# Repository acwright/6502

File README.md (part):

6502-COB
========

An **AC6502** retro-style 8-bit computer based on the **65C02** microprocessor.

> 📖 **Guide:** [AC6502 Documentation](https://acwright.github.io/6502-DOCS/) — the user's and programmer's guide for the whole family.
> See [COB's page in the family appendix](https://acwright.github.io/6502-DOCS/family/cob).

---

## Table of Contents

- [Overview](#overview)
- [Architecture](#architecture)
- [Systems](#systems)
- [Software](#software)
- [Hardware](#hardware)
  - [Backplanes](#backplanes)
  - [Cards](#cards)
  - [Helpers](#helpers)
- [Firmware](#firmware)
  - [KEH Controller](#keh-controller)
  - [PS2 Keyboard Controller](#ps2-keyboard-controller)
  - [STP Controller](#stp-controller)
- [CAD](#cad)
- [Production](#production)
- [Schematics](#schematics)
- [Checking the schematics](#checking-the-schematics)
- [Libraries](#libraries)
- [Bill of Materials](#bill-of-materials)
  - [Backplane](#backplane)
  - [Backplane Helper](#backplane-helper)
  - [Backplane Pro](#backplane-pro)
  - [Blinkenlights Card](#blinkenlights-card)
  - [Breadboard Helper](#breadboard-helper)
  - [Clock Helper](#clock-helper)
  - [CPU Card](#cpu-card)
  - [CPU Card Pro](#cpu-card-pro)
  - [DB25 Helper](#db25-helper)
  - [GPIO Breadboard Helper](#gpio-breadboard-helper)
  - [GPIO Card](#gpio-card)
  - [GPIO Helper](#gpio-helper)
  - [Joystick Helper](#joystick-helper)
  - [Keyboard Encoder Helper](#keyboard-encoder-helper)
  - [Keyboard Helper](#keyboard-helper)
  - [LCD Board](#lcd-board)
  - [LCD Card](#lcd-card)
  - [Mega Helper](#mega-helper)
  - [Memory Card](#memory-card)
  - [Prototype Card](#prototype-card)
  - [PS2 Helper](#ps2-helper)
  - [RAM Card](#ram-card)
  - [RTC Card](#rtc-card)
  - [Serial Card](#serial-card)
  - [Serial Card Pro](#serial-card-pro)
  - [Sound Card](#sound-card)
  - [Storage Card](#storage-card)
  - [Storage Card Pro](#storage-card-pro)
  - [VERA Helper](#vera-helper)
  - [VGA Card](#vga-card)
  - [VGA Card Pro](#vga-card-pro)
  - [Video Card](#video-card)
  - [Video Card Pro](#video-card-pro)
- [Purchase](#purchase)
- [License](#license)

---

## Overview

The AC6502 ecosystem is a family of open-source, 65C02-based computers sharing a common architecture, memory map, and [BIOS](https://github.com/acwright/6502-BIOS). Each computer in the family is purpose-built for a different use case but runs the same software and firmware.

The **COB** (Computer on a Backplane) is a full-featured modular desktop computer. It features a real 65C02 CPU, a backplane architecture with expandable card slots, up to 544KB RAM, composite or VGA video output, CompactFlash or SD storage, a real-time clock, and support for PS/2 keyboards, matrix keyboards, and Atari 2600-compatible joysticks.

## Architecture

All AC6502 computers share:

- **CPU**: 65C02 (or accurate emulation)
- **Memory**: 32KB RAM + 32KB ROM, with optional banked RAM expansion
- **Memory Map**: Standardized across the ecosystem — zero page, stack, I/O space ($8000–$9FFF), system ROM, and interrupt vectors at $FFFA–$FFFF
- **Bus**: 16-bit address bus, 8-bit bidirectional data bus, standard 65C02 control signals (RW, PHI2, RESET, IRQ, NMI, RDY, SYNC)
- **BIOS**: A common [BIOS](https://github.com/acwright/6502-BIOS) provides the kernel, monitor, and BASIC interpreter across all systems

## Systems

| Project | Description |
|---------|-------------|
| [6502-ACE](https://github.com/acwright/6502-ACE) | All-in-one Computer Experience — A single board computer |
| [6502-COB](https://github.com/acwright/6502-COB) | Computer On a Backplane — Modular desktop computer with expandable card slots (YOU ARE HERE) |
| [6502-DEV](https://github.com/acwright/6502-DEV) | Development Environment Vehicle — Emulation-based dev system |
| [6502-KIM](https://github.com/acwright/6502-KIM) | Keypad Input Monitor - KIM-1 inspired minimal computer |
| [6502-VCS](https://github.com/acwright/6502-VCS) | Video Computer System — Cartridge-based retro gaming console |

## Software

| Project | Description |
|---------|-------------|
| [6502-BIOS](https://github.com/acwright/6502-BIOS) | The shared BIOS (kernel, monitor, BASIC) for all AC6502 computers |
| [6502-EMULATOR](https://github.com/acwright/6502-EMULATOR) | Emulator for the whole family — desktop app, browser build, and a command line for scripted runs |
| [6502-PRG](https://github.com/acwright/6502-PRG) | Template project for writing assembly language programs |
| [6502-CRT](https://github.com/acwright/6502-CRT) | Template project for writing assembly language cartridges |
| [6502-ASM](https://github.com/acwright/6502-ASM) | Assembly language example programs and demos |
| [6502-BAS](https://github.com/acwright/6502-BAS) | BASIC program listings |
| [6502-WOZMON](https://github.com/acwright/6502-WOZMON) | Wozmon as a standalone ROM |
| [6502-NOP](https://github.com/acwright/6502-NOP) | An all-NOP ROM, for probing a board during bring-up |
| [6502-DOCS](https://github.com/acwright/6502-DOCS) | The documentation site — the guide, the printable reference cards, branding and label artwork |
| [cffs](https://github.com/acwright/cffs) | Builds CompactFlash disk images for the BIOS filesystem |
| [bastok](https://github.com/acwright/bastok) | Tokenizes BASIC listings into `.prg` images, and back |
| [bin2woz](https://github.com/acwright/bin2woz) | Converts a binary into a Wozmon serial upload |

## Hardware

This repository contains KiCad 7.0+ PCB designs for the backplanes, cards, and helpers that make up the COB system.

### Backplanes

**`Hardware/Backplane/`** — Passive backplane providing 5 card slots with full bus interconnect across all slots.

**`Hardware/Backplane Pro/`** — Enhanced backplane with integrated clock generation, reset circuitry, and power distribution plus 5 card slots. Rev 1.1 moves to entirely through-hole components and adds an onboard power switch and DC barrel jack input.

**`Hardware/Backplane Helper/`** — Adds additional card slots to expand the total backplane configuration up to 12 slots.

### Cards

**`Hardware/CPU Card/`** — Hosts the 65C02 CPU in a card form factor for backplane-based COB systems.

**`Hardware/CPU Card Pro/`** — Hosts a 65816 16-bit CPU (backward-compatible with 65C02). *(Untested)*

**`Hardware/Memory Card/`** — Provides 32KB SRAM and 32KB EEPROM with address decoding logic for COB systems using the CPU Card.

**`Hardware/RAM Card/`** — 512KB banked RAM expansion organized as two 256KB banks with 256 × 1KB windows each.

**`Hardware/RTC Card/`** — Real-time clock via Dallas DS1511Y with battery backup and 256 bytes of battery-backed SRAM.

**`Hardware/GPIO Card/`** — General-purpose I/O via 65C22 VIA supporting keyboards, joysticks, timers, and custom devices.

**`Hardware/Serial Card/`** — RS-232 serial communication via 65C51 ACIA and MAX232 level shifter.
Female DB-9 wired as **DCE**, so a straight-through cable reaches a PC. `DCD` and `DSR` are tied to
ground; `DTR` is not connected. The `CTS EN` jumper (J4) picks whether the ACIA's `CTS` comes from
ground or from the cable — **ground is the default**, which leaves the transmitter always free to
send.

**`Hardware/Serial Card Pro/`** — Enhanced serial card with full modem control signals (DTR, DCD, DSR).
Male DB-9 wired as **DTE**, like a PC, so reaching a laptop needs a **null-modem** cable — unlike the
plain Serial Card. `CTS`, `DSR` and `DTR` always reach the cable; the `DCD EN` jumper picks ground or
the cable for `DCD` — **ground is the default**.

**The handshake lines are not decoration.** On a real R6551, measured on a KIM in 2026: `CTS` high
stops the transmitter dead, and `DCD` high stops the receiver and the arriving byte is lost. A card
jumpered to take either from the cable, plugged into something that does not assert them, looks like
a dead board — no banner, no echo — until the line comes back. Ground is the default for exactly
that reason.

**`Hardware/VGA Card/`** — VGA 640×480 video output via Raspberry Pi Pico running [Pico9918](https://github.com/visrealm/pico9918) with TMS9918A-compatible graphics modes.

**`Hardware/VGA Card Pro/`** — Fully programmable VGA output using Pi Pico with custom firmware. *(Untested)*

**`Hardware/Video Card/`** — Composite video output via TMS9918A Video Display Processor with 16KB video RAM.

**`Hardware/Video Card Pro/`** — Enhanced composite video card. *(Untested)*

**`Hardware/Sound Card/`** — 3-voice SID audio output via ARMSID module with RCA line-level output.

**`Hardware/Storage Card/`** — CompactFlash storage interface supporting up to 128GB via IDE-compatible protocol.

**`Hardware/Storage Card Pro/`** — SD card (up to 32GB) and 16MB onboard SPI flash storage interface. *(Untested, experimental — the stock BIOS has no driver for it; see [STP Controller](#stp-controller))*

**`Hardware/LCD Card/`** — 16×2 character LCD display via 65C22 VIA in 4-bit or 8-bit mode.

**`Hardware/Blinkenlights Card/`** — Visual bus monitoring with LEDs showing address bus (16), data bus (8), and control signals (8) in real time.

**`Hardware/Prototype Card/`** — Blank prototyping area with integrated breadboard and full bus access headers.

### Helpers

**`Hardware/Keyboard Encoder Helper/`** — ATmega1284p-based dual keyboard encoder supporting PS/2 keyboard and 8×8 matrix keyboard simultaneously via 65C22 VIA.

**`Hardware/PS2 Helper/`** — ATmega328p-based PS/2 keyboard bridge that drives an MT8808 analog crosspoint switch to emulate a matrix keyboard. Its output is a raw 8×8 matrix and feeds the matrix inputs of a Keyboard Encoder Helper, which is what talks to the 65C22 VIA — not the VIA directly.

**`Hardware/Keyboard Helper/`** — 64-key matrix keyboard with Atari 2600-compatible joystick support.

**`Hardware/GPIO Helper/`** — 8 buttons and 8 LEDs for testing and debugging GPIO Card connections.

**`Hardware/GPIO Breadboard Helper/`** — Breadboard interface adapter for the GPIO Card.

**`Hardware/Joystick Helper/`** — Atari 2600-style dual joystick connector and interface board.

**`Hardware/Clock Helper/`** — Manual clock control providing single-step, free-run, and halt modes for debugging real CPU systems.

**`Hardware/DB25 Helper/`** — GPIO to DB25 connector adapter for external device interfacing.

**`Hardware/Breadboard Helper/`** — Exposes the full AC6502 bus to a breadboard for prototyping and experimentation.

**`Hardware/Mega Helper/`** — Arduino Mega 2560 interface adapter for the AC6502 bus.

**`Hardware/LCD Board/`** — 320×240 TFT LCD display (ILI9341) interfaced via 65C22 VIA. *(Untested)*

**`Hardware/VERA Helper/`** — VERA FPGA video module adapter for the AC6502 bus.

## Firmware

This repository contains [PlatformIO](https://platformio.org/)-based firmware for the COB system's microcontroller helpers.

### KEH Controller
`Firmware/KEH Controller/`

Firmware for the ATmega1284p on the Keyboard Encoder Helper. Provides:

- Simultaneous PS/2 keyboard and 8×8 matrix keyboard scanning
- ASCII conversion with modifier key support (Shift, Ctrl)
- Buffered, debounced input handling
- Parallel I/O to the AC6502 bus via 65C22 VIA

See [Firmware/KEH Controller/README.md](./Firmware/KEH%20Controller/README.md) for setup and usage instructions.

### PS2 Keyboard Controller
`Firmware/PS2 Keyboard Controller/`

Firmware for the ATmega328p on the PS2 Helper. Provides:

- Interrupt-driven PS/2 keyboard scan code reading
- MT8808 analog crosspoint switch matrix control
- Make/break detection and extended scan code support
- Function key emulation via FN key combinations

The MT8808 closes row/column contacts in place of physical key switches, so this
card connects to the **matrix inputs of a Keyboard Encoder Helper**, not to a
65C22 VIA. The encoder does the scanning and ASCII conversion; wired straight to
a VIA the card produces nothing, as the BIOS has no matrix-scanning code.

See [Firmware/PS2 Keyboard Controller/README.md](./Firmware/PS2%20Keyboard%20Controller/README.md) for setup and usage instructions.

### STP Controller
`Firmware/STP Controller/`

Firmware for the ATmega328p on the Storage Card Pro. Provides:

- Memory-mapped SPI controller for 6502 bus access
- Support for SD card, 16MB SPI flash, and external SPI devices
- Dual-speed SPI (4 MHz normal operation, 400 kHz initialization)
- PHI2-synchronized interface for reliable 6502 communication

⚠️ **Experimental.** The Storage Card Pro is not part of the default I/O set the
BIOS probes for, and no COB machine is built around it today. The BIOS storage
slot expects eight True IDE CompactFlash registers at `$8C00–$8C07`; this card
presents two SPI registers instead, so a stock BIOS reports `NO DEVICE` for every
storage path. Using it needs a modified BIOS or software that drives the two
registers directly.

See [Firmware/STP Controller/README.md](./Firmware/STP%20Controller/README.md) for setup and usage instructions.

## CAD
`CAD/`

3D-printable enclosure parts and laser-cut top panels for the COB system.

## Production
`Production/`

JLCPCB-ready Gerber files and BOM/CPL for PCB fabrication and assembly.

## Schematics
`Schematics/`

PDF schematics for each board.

## Checking the schematics
`Tests/check-schematics.mjs`

The RAM Card's bank latch decides which kilobyte of its 512 KB each window shows, and a latch that loads on the wrong address corrupts a bank without any sign. The ACE's equivalent latch was wrong twice while its gates looked right on paper, so this script checks the logic instead of reading it. It asks KiCad for the card's netlist, builds the glue logic from the gates it finds there, fits the card's jumpers, and drives every address, as a read and as a write, with PHI2 high and low. That is 262,144 bus states. For each one it compares the RAM's chip select, read and write strobes and A18, and the latch enable, against the memory map, and checks that the card drives the data bus only on a read of its own window. A net that nothing drives counts as a failure, so a missing wire fails too.

It checks the RAM Card Rev 1.0 with both windows jumpered, IO 1 (`$8000`) and IO 2 (`$8400`), which is the only setting Rev 1.0 supports: R1 and R2 pull the window selects to ground, so a window left without a jumper is selected at every address.

Run it after any change to a checked schematic:

```sh
node Tests/check-schematics.mjs
```

It needs Node.js and KiCad's `kicad-cli`, which it finds on the `PATH`, at the macOS default location, or through a `KICAD_CLI` environment variable. It takes a few seconds, prints `ok` or `FAIL` for each check with example bus states for any failure, and exits non-zero on a failure.

## Libraries
`Libraries/`

Shared KiCad symbol and footprint libraries used across all AC6502 hardware projects.

## Bill of Materials

### Backplane

| Reference | Qty | Value | Description | DigiKey | Mouser |
|-----------|-----|-------|-------------|---------|--------|
| J1–J5 | 5 | 6502 Card Connector | Card Edge 2×20 | [A31723-ND](https://www.digikey.com/en/products/filter?keywords=A31723-ND) | [571-5-5530843-4](https://www.mouser.com/ProductDetail/571-5-5530843-4) |
| J6, J7 | 2 | 6502 Bus | Bus Connector 2×20 | [732-5401-ND](https://www.digikey.com/en/products/filter?keywords=732-5401-ND) | |

### Backplane Helper

| Reference | Qty | Value | Description | DigiKey | Mouser |
|-----------|-----|-------|-------------|---------|--------|
| J1, J2 | 2 | 6502 Card Connector | Card Edge 2×20 | [A31723-ND](https://www.digikey.com/en/products/filter?keywords=A31723-ND) | [571-5-5530843-4](https://www.mouser.com/ProductDetail/571-5-5530843-4) |
| J3 | 1 | 6502 Bus | Bus Connector 2×20 | [732-5401-ND](https://www.digikey.com/en/products/filter?keywords=732-5401-ND) | |

### Backplane Pro

#### Rev 1.1

| Reference | Qty | Value | Description | Mouser |
|-----------|-----|-------|-------------|--------|
| C1, C3 | 2 | 10uF | Polarized capacitor | |
| C2 | 1 | 100nF | Unpolarized capacitor | |
| D1 | 1 | LED | Power LED 3mm | |
| J1 | 1 | 5V DC | DC Barrel Jack | [640-DCJ200-10-A-K1-K](https://www.mouser.com/ProductDetail/640-DCJ200-10-A-K1-K) |
| J2–J4, J7, J8 | 5 | 6502 Card Connector | Card Edge 2×20 | [571-5-5530843-4](https://www.mouser.com/ProductDetail/571-5-5530843-4) |
| J5 | 1 | CLOCK ENBL SW | Pin Header 1×2 | |
| J6 | 1 | RESET SW | Pin Header 1×2 | |
| J9 | 1 | 6502 Bus | Bus Connector 2×20 | |
| JP1 | 1 | Solder Jumper | Solder Jumper 2-pole | |
| Q1 | 1 | 2N3904 | NPN Transistor TO-92 | |
| R1 | 1 | 330 | Resistor | |
| R2 | 1 | 1M | Resistor | |
| R3 | 1 | 47k | Resistor | |
| R4 | 1 | 10k | Resistor | |
| R5 | 1 | 1k | Resistor | |
| SW1 | 1 | POWER | SPDT Power Switch | [612-400MSP1R6BLKM6QE](https://www.mouser.com/ProductDetail/612-400MSP1R6BLKM6QE) |
| SW2 | 1 | RESET | Tact Push Button 5mm | |
| U1 | 1 | LM555 | Timer SOIC-8 | |
| X1 | 1 | OCXO-14 | Crystal Oscillator DIP-14 | |

#### Rev 1.0

| Reference | Qty | Value | Description | LCSC | DigiKey | Mouser |
|-----------|-----|-------|-------------|------|---------|--------|
| C1, C3–C14 | 13 | 100nF | Unpolarized capacitor | [C49678](https://www.lcsc.com/search?q=C49678) | | |
| C2 | 1 | 10uF | Polarized capacitor | [C7171](https://www.lcsc.com/search?q=C7171) | | |
| D1 | 1 | 1N5819 | Schottky Diode SOD-323F | [C191023](https://www.lcsc.com/search?q=C191023) | | |
| D2 | 1 | LED | LED 0805 | [C2297](https://www.lcsc.com/search?q=C2297) | | |
| J1 | 1 | PWR_SW | JST XH 1×2 | | [455-2247-ND](https://www.digikey.com/en/products/filter?keywords=455-2247-ND) | |
| J2 | 1 | USB-C | USB 2.0 Type-C Receptacle | [C2988369](https://www.lcsc.com/search?q=C2988369) | | |
| J3 | 1 | RESET_SW | JST XH 1×2 | | [455-2247-ND](https://www.digikey.com/en/products/filter?keywords=455-2247-ND) | |
| J4 | 1 | CLOCK_ENBL_SW | JST XH 1×2 | | [455-2247-ND](https://www.digikey.com/en/products/filter?keywords=455-2247-ND) | |
| J5–J9 | 5 | 6502 Card Connector | Card Edge 2×20 | | [A31723-ND](https://www.digikey.com/en/products/filter?keywords=A31723-ND) | [571-5-5530843-4](https://www.mouser.com/ProductDetail/571-5-5530843-4) |
| J10 | 1 | 6502 Bus | Bus Connector 2×20 | | | |
| Q1 | 1 | SS8050 | NPN Transistor SOT-23 | [C2150](https://www.lcsc.com/search?q=C2150) | | |
| R1 | 1 | 1M | Resistor | [C17514](https://www.lcsc.com/search?q=C17514) | | |
| R2 | 1 | 47k | Resistor | [C17713](https://www.lcsc.com/search?q=C17713) | | |
| R3 | 1 | 1k | Resistor | [C17513](https://www.lcsc.com/search?q=C17513) | | |
| R4 | 1 | 10k | Resistor | [C17414](https://www.lcsc.com/search?q=C17414) | | |
| R5, R6 | 2 | 5.1k | Resistor | [C27834](https://www.lcsc.com/search?q=C27834) | | |
| R7 | 1 | 330 | Resistor | [C17630](https://www.lcsc.com/search?q=C17630) | | |
| SW1 | 1 | Reset | Push Button | [C318884](https://www.lcsc.com/search?q=C318884) | | |
| U1 | 1 | LM555xM | Timer SOIC-8 | [C7593](https://www.lcsc.com/search?q=C7593) | | |
| X1 | 1 | OCXO-14 | Crystal Oscillator DIP-14 | | | |

### Blinkenlights Card

| Reference | Qty | Value | Description | LCSC |
|-----------|-----|-------|-------------|------|
| C1–C4 | 4 | 100nF | Unpolarized capacitor | [C49678](https://www.lcsc.com/search?q=C49678) |
| D1–D25 | 25 | LED | LED 0805 | [C2297](https://www.lcsc.com/search?q=C2297) |
| D26, D27 | 2 | LED | LED 0805 | [C2295](https://www.lcsc.com/search?q=C2295) |
| D28–D30 | 3 | LED | LED 0805 | [C2296](https://www.lcsc.com/search?q=C2296) |
| D31, D32 | 2 | LED | LED 0805 | [C2293](https://www.lcsc.com/search?q=C2293) |
| R1–R32 | 32 | 330 | Resistor | [C17630](https://www.lcsc.com/search?q=C17630) |
| U1, U2, U4 | 3 | 74HC573 | 8-bit Latch SOIC-20 | [C5608](https://www.lcsc.com/search?q=C5608) |
| U3 | 1 | 74HC04 | Hex Inverter SOIC-14 | [C5590](https://www.lcsc.com/search?q=C5590) |

### Breadboard Helper

| Reference | Qty | Value | Description | DigiKey |
|-----------|-----|-------|-------------|---------|
| J1 | 1 | 6502 Bus | Bus Connector 2×20 | [732-5401-ND](https://www.digikey.com/en/products/filter?keywords=732-5401-ND) |
| J2, J3 | 2 | Pin Header | Pin Header 1×20 | |

### Clock Helper

| Reference | Qty | Value | Description |
|-----------|-----|-------|-------------|
| C1 | 1 | 100nF | Capacitor |
| D1, D2 | 2 | LED | LED 3mm |
| J1 | 1 | IO | Pin Header 1×5 |
| R1–R5 | 5 | 1k | Resistor |
| R6–R8 | 3 | 330 | Resistor |
| SW1, SW2 | 2 | XKB5858-Z | DPDT Toggle Switch |
| SW3 | 1 | XKB5858-W | DPDT Toggle Switch |
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
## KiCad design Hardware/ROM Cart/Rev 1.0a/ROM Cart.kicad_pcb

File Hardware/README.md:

6502 Hardware
=============

This folder contains KiCad hardware designs for all PCBs in the 6502 project. Each design includes complete schematics, PCB layouts, and component libraries.

---

## Table of Contents

- [Overview](#overview)
- [Folder Structure](#folder-structure)
- [Hardware Categories](#hardware-categories)
- [Design Standards](#design-standards)
- [Assembly Notes](#assembly-notes)
- [Revision History](#revision-history)

---

## Overview

The 6502 project hardware is organized into four main categories:

1. **Boards**: Core system boards (mainboards, backplanes, development boards)
2. **Cards**: Peripheral expansion cards that plug into backplane slots
3. **Helpers**: Interface boards that provide specific functionality or connectors
4. **Carts**: Cartridge boards for ROM images

All designs are created using **KiCad 7.0+** and optimized for manufacturing by **JLCPCB**. Designs use a mix of surface-mount (SMD) and through-hole (DIP/TH) components for optimal balance of manufacturability and hobbyist assembly.

---

## Folder Structure

```
Hardware/
├── <BoardName>/
│   ├── Rev X.X/
│       ├── <BoardName>.kicad_pro    # KiCad project file
│       ├── <BoardName>.kicad_sch    # Schematic file
│       ├── <BoardName>.kicad_pcb    # PCB layout file
│       ├── fp-lib-table              # Footprint library table
│       └── sym-lib-table             # Symbol library table
└── ...
```

Each board folder contains one or more revision subfolders. Always use the latest revision unless specifically maintaining compatibility with older versions.

---

## Design Standards

All hardware designs follow these standards for consistency and manufacturability:

### PCB Specifications

**Layers:**
- Simple boards: 2-layer

**Dimensions:**
- Card width: 100mm
- Card height: 60mm
- Board width: 100mm
- Board height: 100mm
- Helper width: 100mm
- Helper height: 50mm
- PCB thickness: 1.6mm standard

**Trace Width:**
- Signal traces: 0.254mm (10 mil) minimum, 0.381mm (15 mil) typical
- Power traces: 0.508mm (20 mil) minimum, wider for high current
- Clearance: 0.254mm (10 mil) minimum

**Vias:**
- Standard: 0.6mm drill, 1.0mm pad
- Power: 0.8mm drill, 1.2mm pad
- Minimum: 0.3mm drill, 0.6mm pad

**JLCPCB Compatibility:**
- All designs pass JLCPCB design rules (see Production folder)
- Component selection optimized for JLCPCB assembly catalog
- Alternative footprints provided where JLCPCB parts unavailable

### Component Selection

**IC Packages:**
- Through-hole (DIP): For CPUs, RAM, ROM, socketed ICs
- SMD (SOIC, TSSOP, QFN): For modern ICs, microcontrollers, buffers

**Passive Components:**
- SMD: 0805 or 1206 packages (hand-solderable)
- Through-hole: 1/8W resistors, radial capacitors (when space allows)

**Connectors:**
- Through-hole: For all connectors (mechanical stress consideration)
- IDC headers: 2.54mm pitch for ribbon cables
- Card edge: Gold-plated fingers for backplane cards

### Schematic Conventions

**Net Naming:**
- Address bus: A0-A15
- Data bus: D0-D7
- Control signals: PHI2, RWB, RESB, IRQB, NMIB, etc.
- Power: +5V or VCC, GND
- Chip enables: CS, CSB (active low)

**Component References:**
- U: Integrated circuits
- R: Resistors
- C: Capacitors
- D: Diodes
- Q: Transistors
- J: Connectors/headers
- SW: Switches
- LED: LEDs
- Y: Crystals/oscillators

**Component Values:**
- Resistors: Ohms (100R, 1K, 10K)
- Capacitors: Farads (100nF, 10μF, 100μF)
- Inductors: Henries (10μH, 100μH)

---

## Assembly Notes

### Component Orientation

**ICs in DIP sockets:**
- Pin 1 indicator (notch or dot) must align with socket and PCB marking
- CPU, RAM, ROM: Check datasheets for pin 1 location

**Electrolytic capacitors:**
- Polarity marked on PCB (+ and -)
- Negative stripe on capacitor body aligns with - on PCB

**Diodes:**
- Cathode band aligns with band on PCB silkscreen

**LEDs:**
- Longer lead (anode) to + pad
- Flat side (cathode) to - pad or square pad

### Soldering Tips

**Through-hole:**
- Insert component from top, bend leads on bottom
- Apply soldering iron to pad + lead simultaneously
- Feed solder to junction (not to iron tip)
- Remove iron then solder wire
- Ideal joint: shiny, concave fillet

**SMD (if hand-soldering):**
- Use fine-tip soldering iron (conical tip)
- Apply flux to pads
- Tack one corner pin first
- Solder remaining pins
- Check for bridges with magnification
- Use solder wick to remove bridges

**IC sockets:**
- Tack opposite corner pins first
- Solder all remaining pins
- Check alignment before soldering all pins

### DRC (Design Rules Check) Verification

Before ordering PCBs, run DRC in KiCad:
1. Open PCB layout in KiCad
2. Select Tools → Design Rules Checker
3. Load JLCPCB design rules (if available in Production folder)
4. Run DRC
5. Fix all errors (warnings acceptable if understood)

Common errors:
- Trace too thin (minimum 0.127mm outer layer)
- Clearance too small (minimum 0.127mm)
- Via drill too small (minimum 0.3mm)
- Silkscreen over pads (warnings, JLCPCB will clip automatically)

---

## Revision History

### Rev 0.0 (Prototyping - 2024)

**Boards:**
- Dev Board

**Known Issues (Rev 1.0):**
- Dev Board 0.0 uses TXS0108 level shifters which were found to be unpredictable on the 6502 bus with some cards

### Rev 1.0 (Initial Release - 2024)

**Boards:**
- Initial designs for all boards
- Backplane, Backplane Pro, Main Board, Dev Board

**Cards:**
- CPU Card, Memory Card, Video Card, VGA Card, Serial Card
- GPIO Card, Sound Card, Storage Card
- Blinkenlights Card, LCD Card, Prototype Card
- RAM Card, RTC Card

**Helpers:**
- Keyboard Encoder Helper, PS2 Helper
- Keypad Helper, Keyboard Helper
- Clock Helper, GPIO Helper, Breadboard Helper
- Joystick Helper, DB25 Helper
- Backplane Helper, Mega Helper

**Carts:**
- ROM Cart

**Known Issues (Rev 1.0):**
- None

### Rev 1.1 (Planned - Future)

**Improvements:**
- TODO

---

## Working with Hardware Designs

### Opening in KiCad

1. Install [KiCad 7.0 or later](https://www.kicad.org/)
2. Clone this repository or download specific board folder
3. Navigate to `Hardware/<BoardName>/Rev X.X/`
4. Open `<BoardName>.kicad_pro` in KiCad

### Viewing Schematics

1. With project open, click "Schematic Editor" icon
2. Navigate multi-sheet schematics with sheet hierarchy (left panel)
3. Use Find tool (Ctrl+F / Cmd+F) to locate specific nets or components

### Viewing PCB Layout

1. With project open, click "PCB Editor" icon
2. Use 3D Viewer (View → 3D Viewer) to see board in 3D
3. Toggle layers (right panel) to examine inner layers, silkscreen, etc.

### Exporting Production Files

See [Production README](../Production/README.md) for detailed export instructions.

Quick export (from PCB Editor):
- Gerbers: File → Fabrication Outputs → Gerbers
- Drill files: File → Fabrication Outputs → Drill Files
- BOM: File → Fabrication Outputs → BOM
- Pick and Place: File → Fabrication Outputs → Footprint Position (.pos) File

---

**For more information, see:**
- [Main README](../README.md) - Project overview and system descriptions
- [Production README](../Production/README.md) - Manufacturing and ordering
- [Firmware README](../Firmware/README.md) - Firmware for microcontroller-based boards
- [Schematics README](../Schematics/README.md) - Schematic viewing and conventions

---

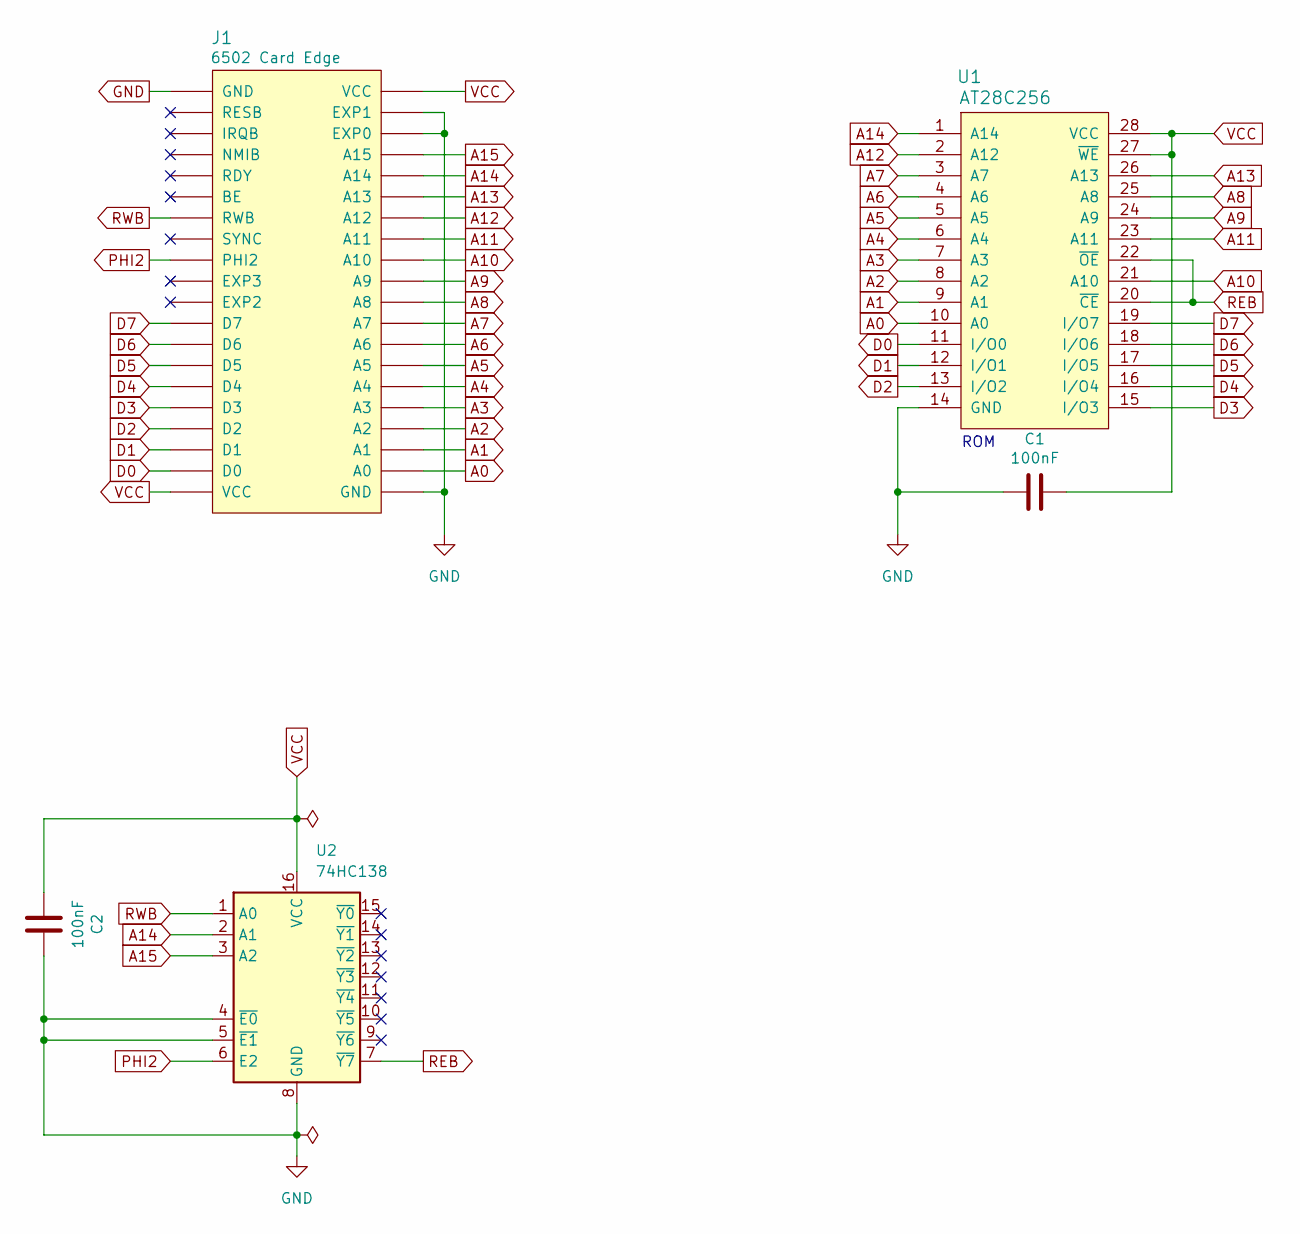
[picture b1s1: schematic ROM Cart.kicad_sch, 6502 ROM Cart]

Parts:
C1, C2: 100nF; C_Disc_D5.0mm_W2.5mm_P5.00mm
J1: 6502 Card Edge
U1: AT28C256; DIP-28_W15.24mm_Socket_LongPads
U2: 74HC138; DIP-16_W7.62mm_Socket_LongPads

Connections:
A0: J1.A0, U1.10 (A0)
A1: J1.A1, U1.9 (A1)
A2: J1.A2, U1.8 (A2)
A3: J1.A3, U1.7 (A3)
A4: J1.A4, U1.6 (A4)
A5: J1.A5, U1.5 (A5)
A6: J1.A6, U1.4 (A6)
A7: J1.A7, U1.3 (A7)
A8: J1.A8, U1.25 (A8)
A9: J1.A9, U1.24 (A9)
A10: J1.A10, U1.21 (A10)
A11: J1.A11, U1.23 (A11)
A12: J1.A12, U1.2 (A12)
A13: J1.A13, U1.26 (A13)
A14: J1.A14, U1.1 (A14), U2.2 (A1)
A15: J1.A15, U2.3 (A2)
D0: J1.D0, U1.11 (I/O0)
D1: J1.D1, U1.12 (I/O1)
D2: J1.D2, U1.13 (I/O2)
D3: J1.D3, U1.15 (I/O3)
D4: J1.D4, U1.16 (I/O4)
D5: J1.D5, U1.17 (I/O5)
D6: J1.D6, U1.18 (I/O6)
D7: J1.D7, U1.19 (I/O7)
GND: C1.2, C2.2, J1.EXP0, J1.EXP1, J1.GND, U1.14 (GND), U2.4 (~E0), U2.5 (~E1), U2.8 (GND)
PHI2: J1.PHI2, U2.6 (E2)
RB: U1.20 (~CE), U1.22 (~OE), U2.7 (~Y7)
RWB: J1.RWB, U2.1 (A0)
VCC: C1.1, C2.1, J1.VCC, U1.27 (~WE), U1.28 (VCC), U2.16 (VCC)

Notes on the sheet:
ROM

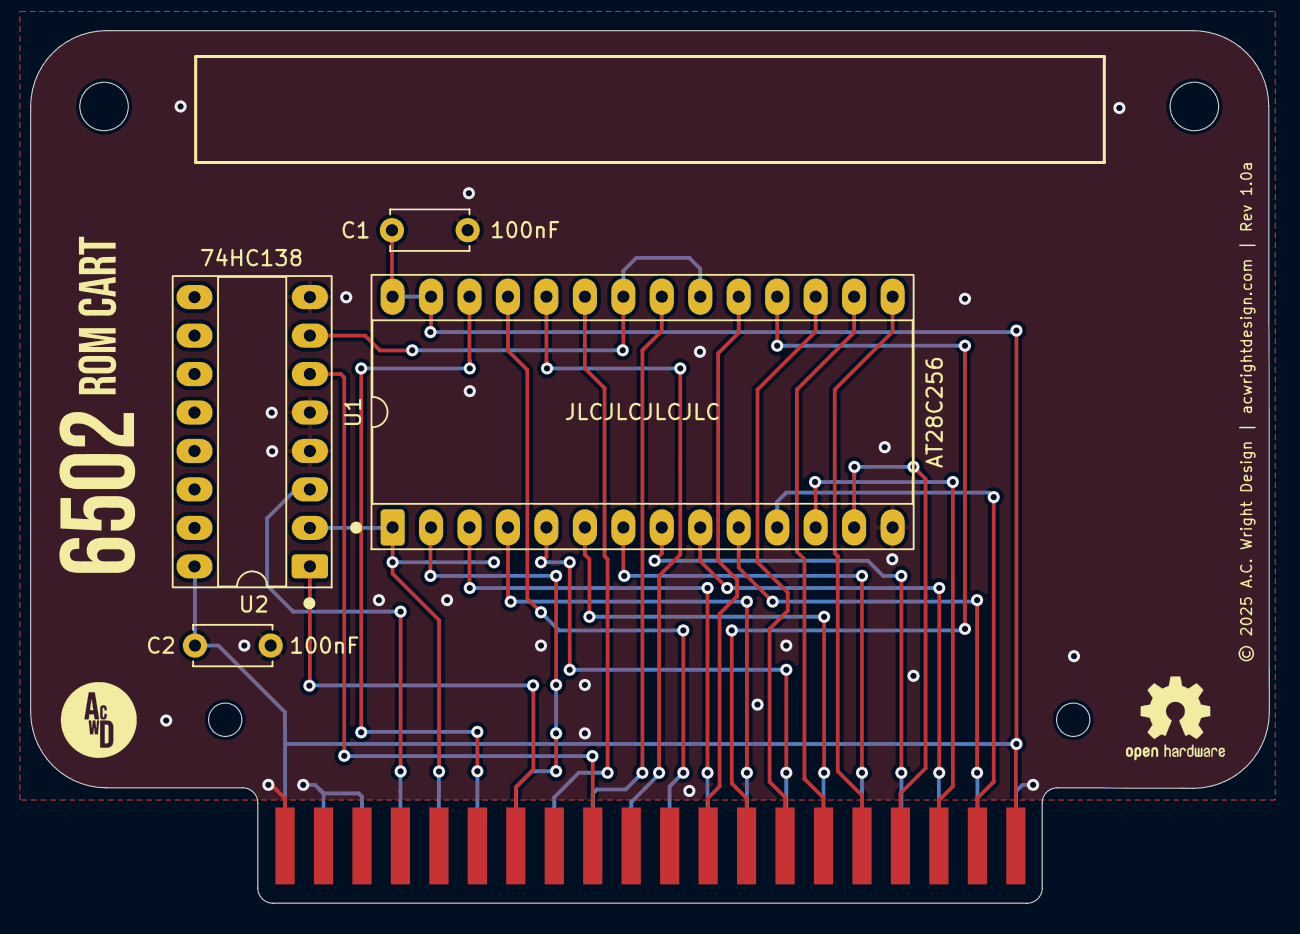
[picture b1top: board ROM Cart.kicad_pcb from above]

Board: 2 copper layers, 81.8 x 57.6 mm, 9 parts (0 on the bottom side), 29 nets.

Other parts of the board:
H1, H2: MountingHole; MountingHole_3.2mm_M3
H3, H4: MountingHole; MountingHole_2.2mm_M2

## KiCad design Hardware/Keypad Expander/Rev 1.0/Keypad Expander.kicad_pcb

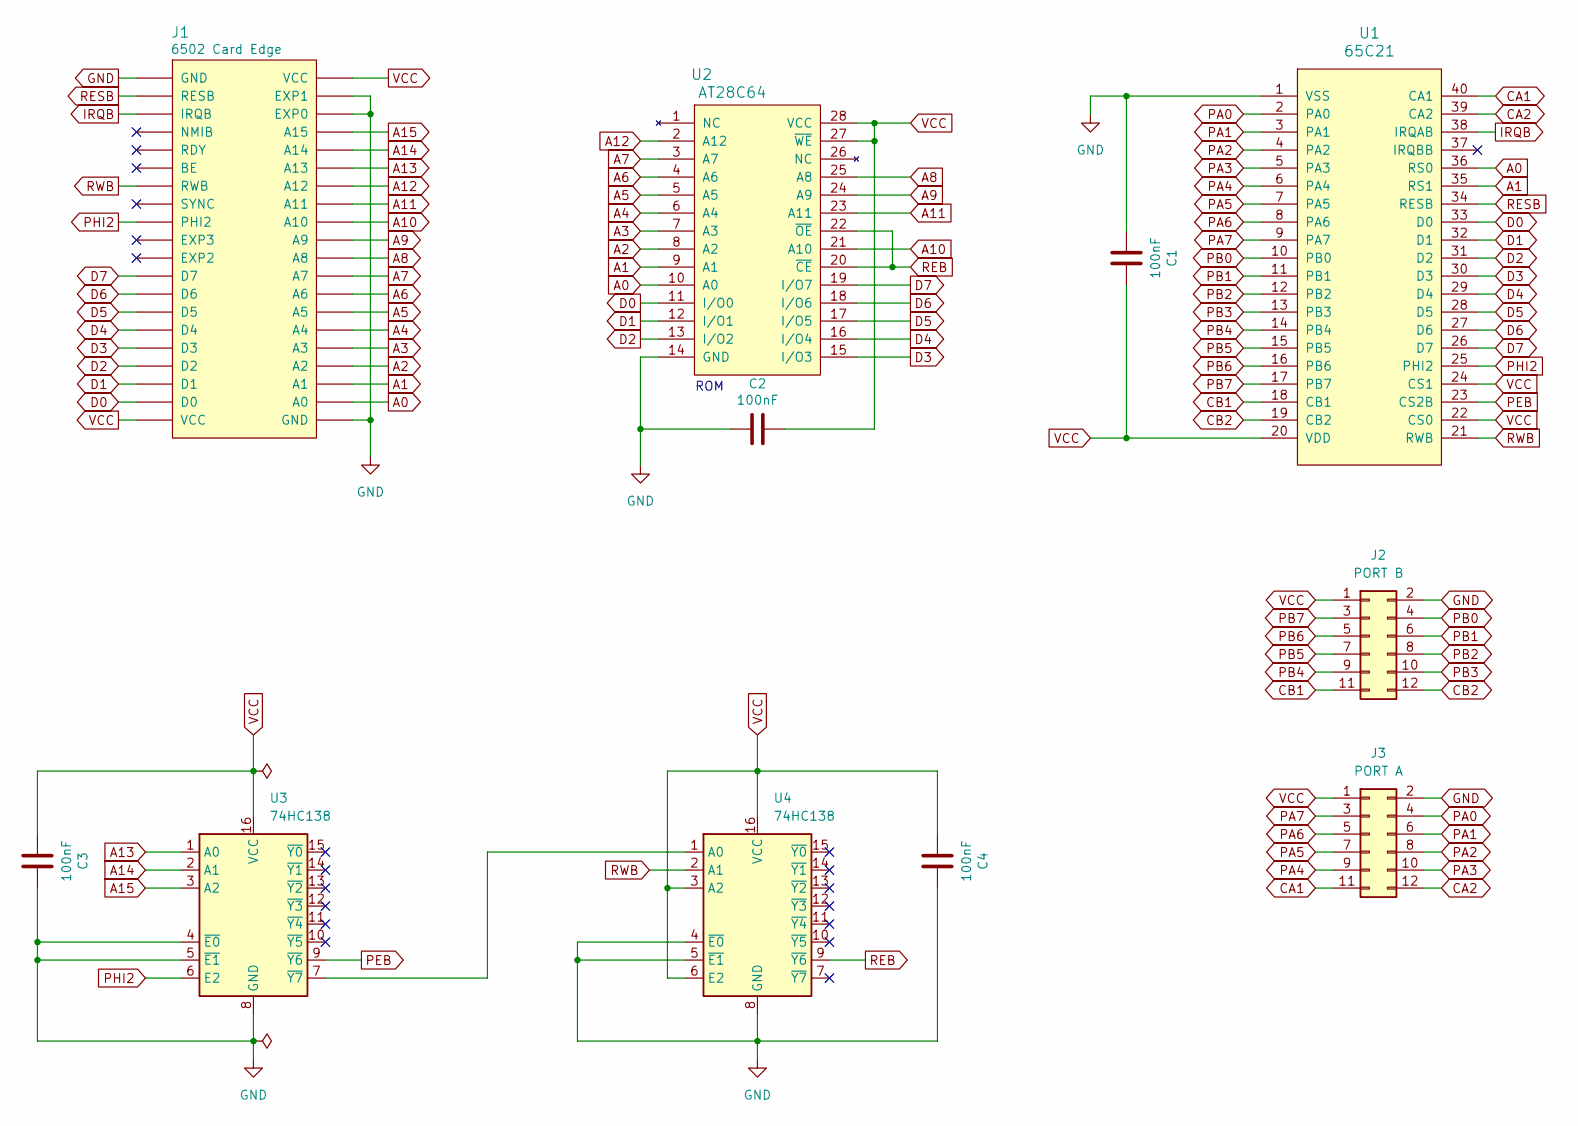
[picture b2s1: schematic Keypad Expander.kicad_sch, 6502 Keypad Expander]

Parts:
C1: 100nF; C_Disc_D5.0mm_W2.5mm_P5.00mm; LCSC C49678
C2, C3, C4: 100nF; C_Disc_D5.0mm_W2.5mm_P5.00mm
J1: 6502 Card Edge
J2: PORT B; 6502 GPIO Connector
J3: PORT A; 6502 GPIO Connector
U1: 65C21; DIP-40_W15.24mm_Socket_LongPads
U2: AT28C64; DIP-28_W15.24mm_Socket_LongPads
U3, U4: 74HC138; DIP-16_W7.62mm_Socket_LongPads

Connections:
A0: J1.A0, U1.36 (RS0), U2.10 (A0)
A1: J1.A1, U1.35 (RS1), U2.9 (A1)
A2: J1.A2, U2.8 (A2)
A3: J1.A3, U2.7 (A3)
A4: J1.A4, U2.6 (A4)
A5: J1.A5, U2.5 (A5)
A6: J1.A6, U2.4 (A6)
A7: J1.A7, U2.3 (A7)
A8: J1.A8, U2.25 (A8)
A9: J1.A9, U2.24 (A9)
A10: J1.A10, U2.21 (A10)
A11: J1.A11, U2.23 (A11)
A12: J1.A12, U2.2 (A12)
A13: J1.A13, U3.1 (A0)
A14: J1.A14, U3.2 (A1)
A15: J1.A15, U3.3 (A2)
CA1: J3.11, U1.40 (CA1)
CA2: J3.12, U1.39 (CA2)
CB1: J2.11, U1.18 (CB1)
CB2: J2.12, U1.19 (CB2)
D0: J1.D0, U1.33 (D0), U2.11 (I/O0)
D1: J1.D1, U1.32 (D1), U2.12 (I/O1)
D2: J1.D2, U1.31 (D2), U2.13 (I/O2)
D3: J1.D3, U1.30 (D3), U2.15 (I/O3)
D4: J1.D4, U1.29 (D4), U2.16 (I/O4)
D5: J1.D5, U1.28 (D5), U2.17 (I/O5)
D6: J1.D6, U1.27 (D6), U2.18 (I/O6)
D7: J1.D7, U1.26 (D7), U2.19 (I/O7)
GND: C1.1, C2.2, C3.2, C4.2, J1.EXP0, J1.EXP1, J1.GND, J2.2, J3.2, U1.1 (VSS), U2.14 (GND), U3.4 (~E0), U3.5 (~E1), U3.8 (GND), U4.4 (~E0), U4.5 (~E1), U4.8 (GND)
IRQB: J1.IRQB, U1.38 (IRQAB)
unnamed: U3.7 (~Y7), U4.1 (A0)
PA0: J3.4, U1.2 (PA0)
PA1: J3.6, U1.3 (PA1)
PA2: J3.8, U1.4 (PA2)
PA3: J3.10, U1.5 (PA3)
PA4: J3.9, U1.6 (PA4)
PA5: J3.7, U1.7 (PA5)
PA6: J3.5, U1.8 (PA6)
PA7: J3.3, U1.9 (PA7)
PB0: J2.4, U1.10 (PB0)
PB1: J2.6, U1.11 (PB1)
PB2: J2.8, U1.12 (PB2)
PB3: J2.10, U1.13 (PB3)
PB4: J2.9, U1.14 (PB4)
PB5: J2.7, U1.15 (PB5)
PB6: J2.5, U1.16 (PB6)
PB7: J2.3, U1.17 (PB7)
PEB: U1.23 (CS2B), U3.9 (~Y6)
PHI2: J1.PHI2, U1.25 (PHI2), U3.6 (E2)
REB: U2.20 (~CE), U2.22 (~OE), U4.9 (~Y6)
RESB: J1.RESB, U1.34 (RESB)
RWB: J1.RWB, U1.21 (RWB), U4.2 (A1)
VCC: C1.2, C2.1, C3.1, C4.1, J1.VCC, J2.1, J3.1, U1.20 (VDD), U1.22 (CS0), U1.24 (CS1), U2.27 (~WE), U2.28 (VCC), U3.16 (VCC), U4.3 (A2), U4.6 (E2), U4.16 (VCC)

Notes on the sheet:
ROM

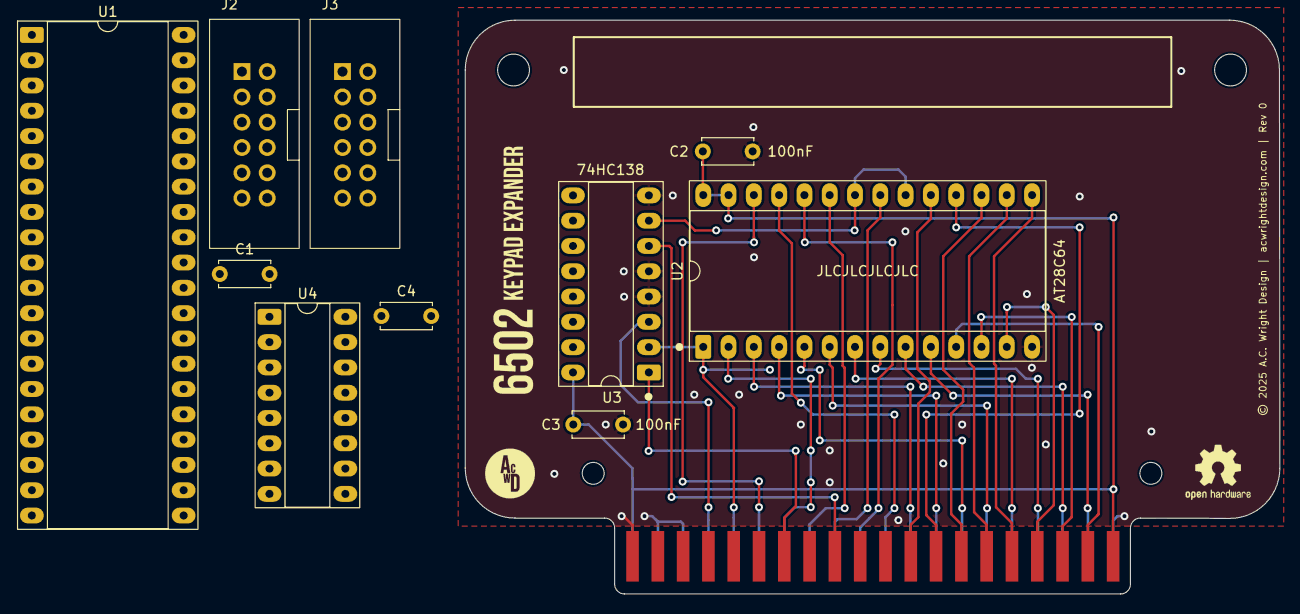
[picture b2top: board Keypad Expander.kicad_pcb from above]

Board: 2 copper layers, 81.8 x 57.6 mm, 15 parts (0 on the bottom side), 53 nets.

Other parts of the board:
H1, H2: MountingHole; MountingHole_3.2mm_M3
H3, H4: MountingHole; MountingHole_2.2mm_M2

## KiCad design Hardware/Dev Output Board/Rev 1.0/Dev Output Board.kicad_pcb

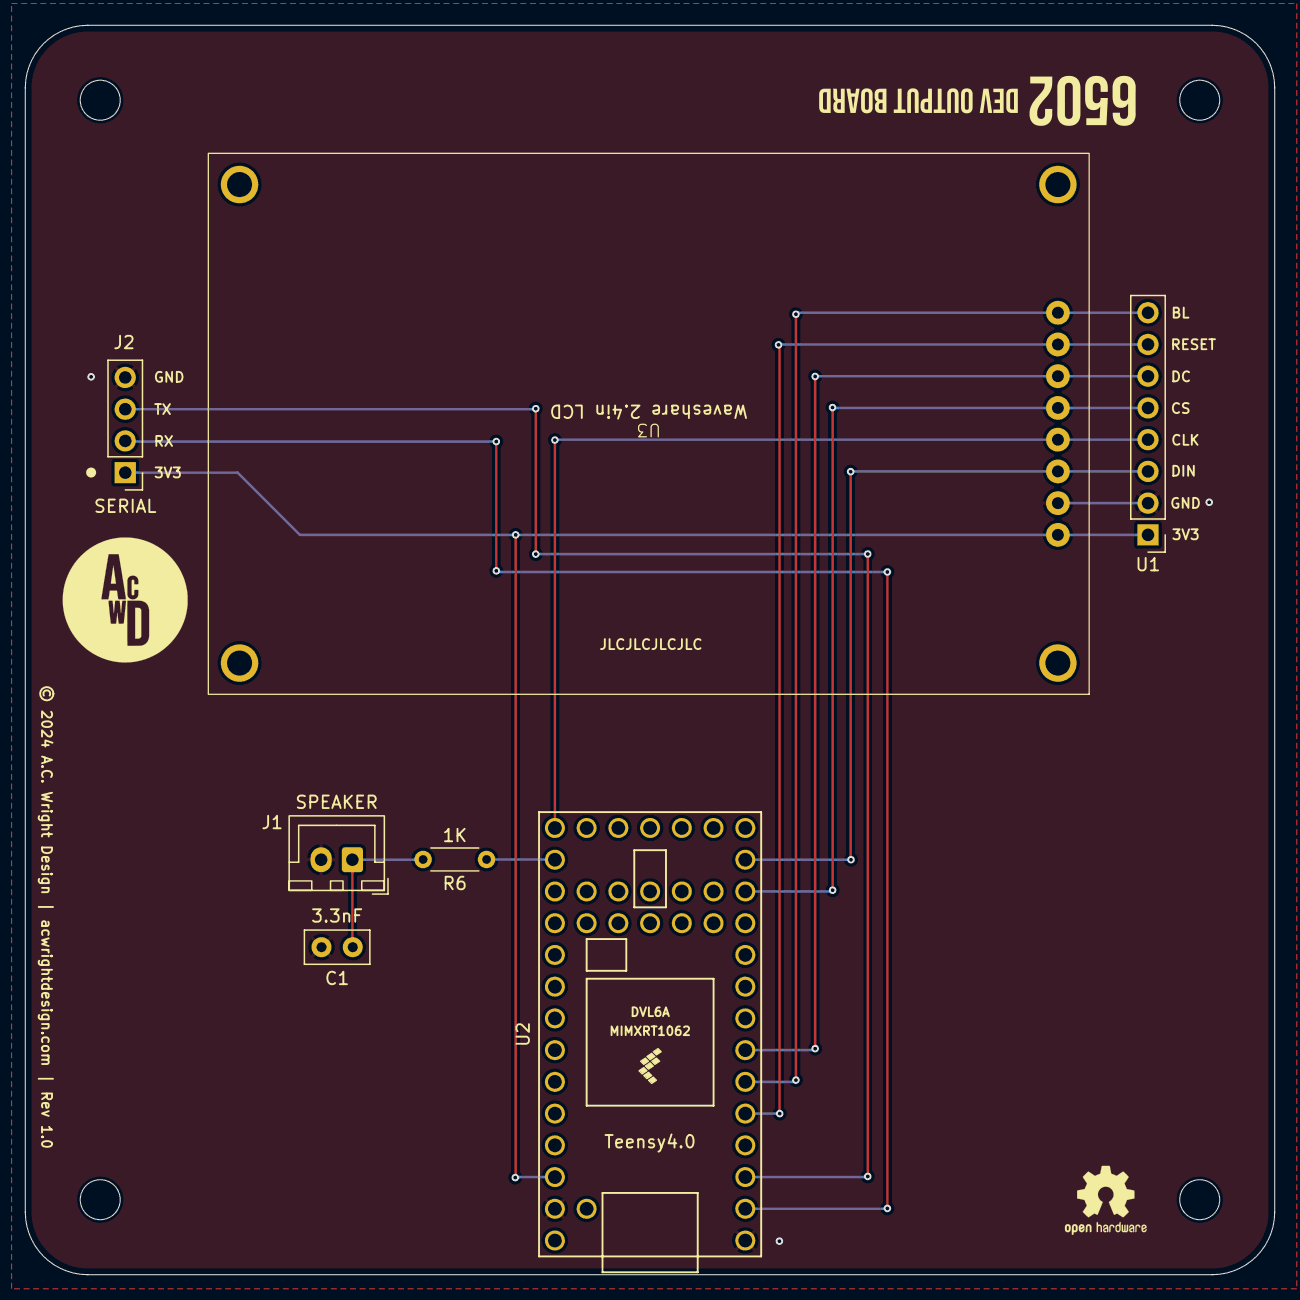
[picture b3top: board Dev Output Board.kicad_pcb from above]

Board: 2 copper layers, 100.0 x 100.0 mm, 11 parts (0 on the bottom side), 12 nets.

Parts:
C1: 3.3nF; C_Disc_D5.0mm_W2.5mm_P2.50mm
H1, H2, H3, H4: MountingHole; MountingHole_3.2mm_M3
J1: SPEAKER; JST_XH_B2B-XH-A_1x02_P2.50mm_Vertical
J2: SERIAL; PinHeader_1x04_P2.54mm_Vertical
R6: 1K; R_Axial_DIN0204_L3.6mm_D1.6mm_P5.08mm_Horizontal
U1: Waveshare 2.4in LCD Header; PinHeader_1x08_P2.54mm_Vertical
U2: Teensy4.0; Teensy40
U3: Waveshare 2.4in LCD

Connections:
3V3: J2.1, U1.1 (VCC), U2.31 (3V3), U3.1 (VCC)
GND: C1.2, J1.2, J2.4, U1.2 (GND), U2.1 (GND), U2.32 (GND), U3.2 (GND)
LCD_BL: U1.8 (BL), U2.6 (4_BCLK2), U3.8 (BL)
LCD_CLK: U1.4 (CLK), U2.20 (13_SCK_CRX1_LED), U3.4 (CLK)
LCD_CS: U1.5 (CS), U2.12 (10_CS_MQSR), U3.5 (CS)
LCD_DATA: U1.3 (DIN), U2.13 (11_MOSI_CTX1), U3.3 (DIN)
LCD_DC: U1.6 (DC), U2.7 (5_IN2), U3.6 (DC)
LCD_RESET: U1.7 (RST), U2.5 (3_LRCLK2), U3.7 (RST)
unnamed: C1.1, J1.1, R6.2
RX: J2.2, U2.2 (0_RX1_CRX2_CS1)
SPEAKER: R6.1, U2.21 (14_A0_TX3_SPDIF_OUT)
TX: J2.3, U2.3 (1_TX1_CTX2_MISO1)

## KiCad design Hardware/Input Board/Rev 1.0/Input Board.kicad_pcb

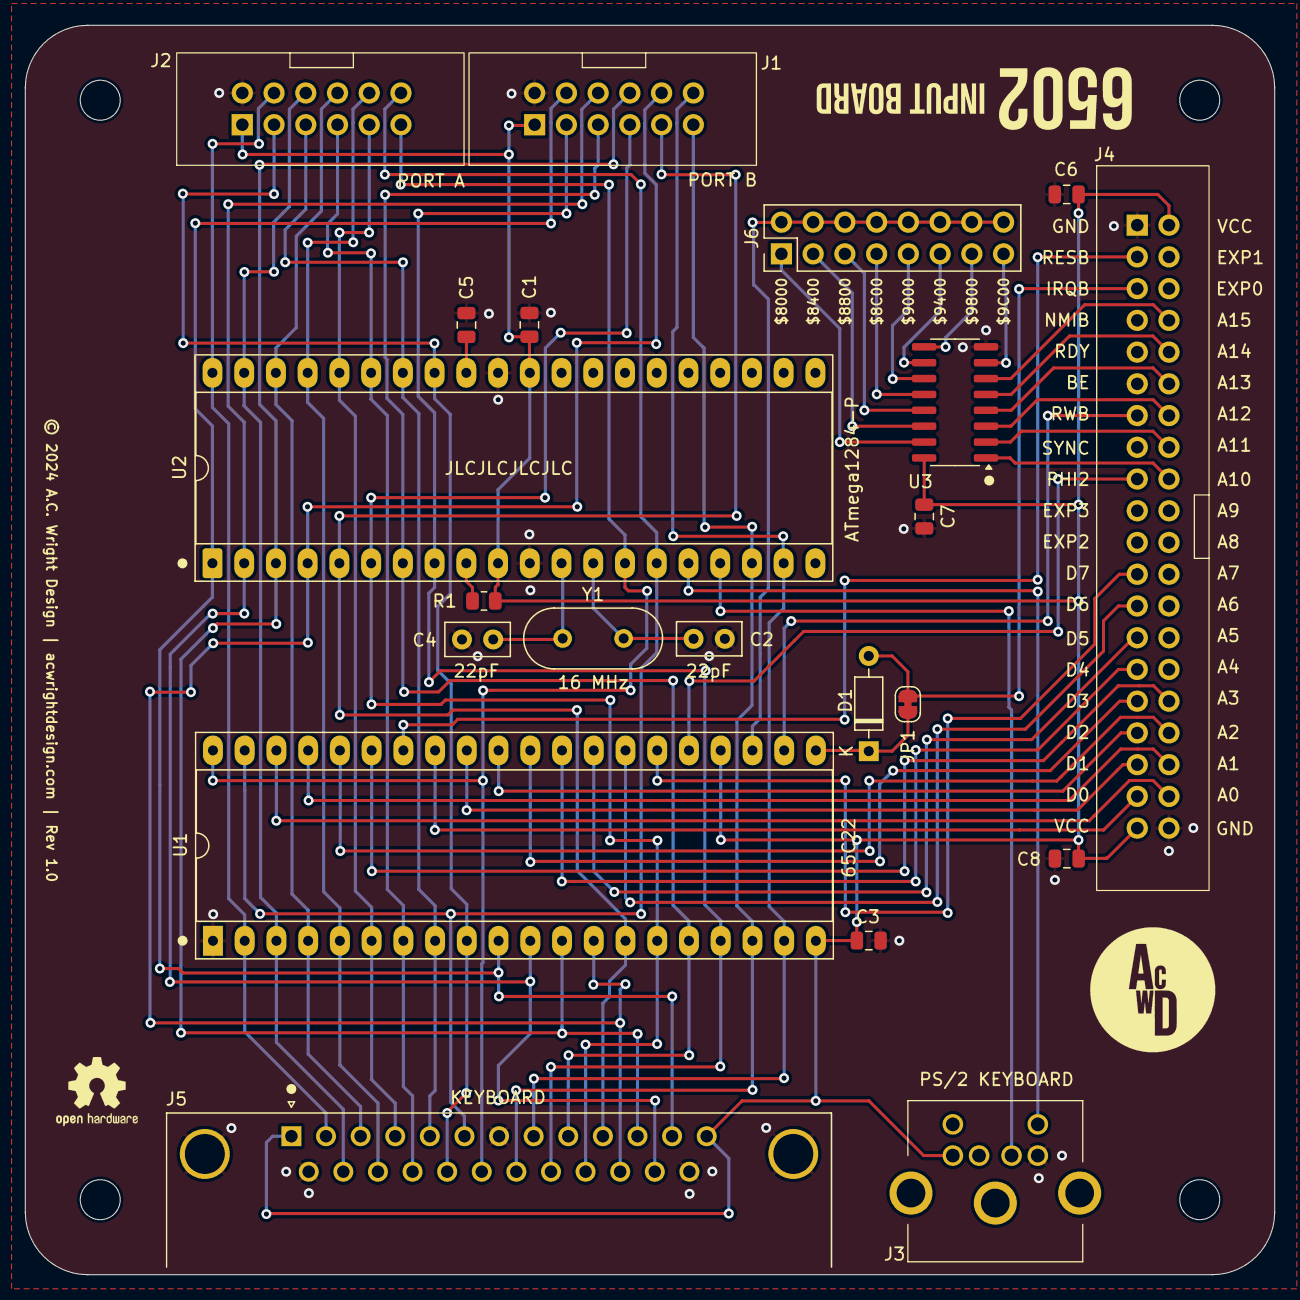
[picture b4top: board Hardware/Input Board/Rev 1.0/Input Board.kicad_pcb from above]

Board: 2 copper layers, 100.0 x 100.0 mm, 25 parts (0 on the bottom side), 60 nets.

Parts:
C1, C3, C5, C6, C7, C8: 100nF; C_0805_2012Metric
C2, C4: 22pF; C_Disc_D5.0mm_W2.5mm_P2.50mm
D1: D_Schottky; D_DO-35_SOD27_P7.62mm_Horizontal
H1, H2, H3, H4: MountingHole; MountingHole_3.2mm_M3
J1: PORT B; 6502 GPIO Connector
J2: PORT A; 6502 GPIO Connector
J3: PS/2 KEYBOARD; KMDGX-6S-BS
J4: 6502 Bus; 6502 Bus Connector
J5: KEYBOARD; DSUB-25_Pins_Horizontal_P2.77x2.84mm_EdgePinOffset7.70mm_Ho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
J6: Conn_02x08_Odd_Even; PinHeader_2x08_P2.54mm_Vertical
JP1: SolderJumper_2_Bridged; SolderJumper-2_P1.3mm_Bridged_RoundedPad1.0x1.5mm
R1: 1K; R_0805_2012Metric
U1: 65C22; DIP-40_W15.24mm_Socket_LongPads
U2: ATmega1284-P; DIP-40_W15.24mm_Socket_LongPads
U3: 74HC138; SOIC-16_3.9x9.9mm_P1.27mm
Y1: 16 MHz; Crystal_HC49-U_Vertical

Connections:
/$8C00: J6.7, U3.12 (~Y3)
/$9C00: J6.15, U3.7 (~Y7)
/$8000: J6.1, U3.15 (~Y0)
/$8400: J6.3, U3.14 (~Y1)
/$8800: J6.5, U3.13 (~Y2)
/$9000: J6.9, U3.11 (~Y4)
/$9400: J6.11, U3.10 (~Y5)
/$9800: J6.13, U3.9 (~Y6)
A0: J4.38, U1.38 (RS0)
A1: J4.36, U1.37 (RS1)
A2: J4.34, U1.36 (RS2)
A3: J4.32, U1.35 (RS3)
A10: J4.18, U3.1 (A0)
A11: J4.16, U3.2 (A1)
A12: J4.14, U3.3 (A2)
A13: J4.12, U3.4 (~E0)
A14: J4.10, U3.5 (~E1)
A15: J4.8, U3.6 (E2)
CA1: J2.11, J5.19, U1.40 (CA1), U2.14 (PD0)
CA2: J2.12, J5.6, U1.39 (CA2), U2.15 (PD1)
CB1: J1.11, J5.20, U1.18 (CB1), U2.18 (PD4)
CB2: J1.12, J5.8, U1.19 (CB2), U2.19 (PD5)
CSB: J6.2, J6.4, J6.6, J6.8, J6.10, J6.12, J6.14, J6.16, U1.23 (CS2B)
D0: J4.37, U1.33 (D0)
D1: J4.35, U1.32 (D1)
D2: J4.33, U1.31 (D2)
D3: J4.31, U1.30 (D3)
D4: J4.29, U1.29 (D4)
D5: J4.27, U1.28 (D5)
D6: J4.25, U1.27 (D6)
D7: J4.23, U1.26 (D7)
GND: C1.1, C2.2, C3.1, C4.2, C5.1, C6.2, C7.2, C8.1, J1.2, J2.2, J3.3, J4.1, J4.40, J5.0 (PAD), J5.7, J5.14, J5.25, U1.1 (VSS), U2.11 (GND), U2.31 (GND), U3.8 (GND)
IRQB: D1.2 (A), J4.5, JP1.2 (B)
unnamed: D1.1 (K), JP1.1 (A), U1.21 (IRQB)
unnamed: C5.2, U2.32 (AREF)
unnamed: C2.1, U2.13 (XTAL1), Y1.2
unnamed: C4.1, U2.12 (XTAL2), Y1.1
unnamed: R1.2, U2.9 (~RESET)
PA0: J2.4, J5.2, U1.2 (PA0), U2.40 (PA0)
PA1: J2.6, J5.15, U1.3 (PA1), U2.39 (PA1)
PA2: J2.8, J5.3, U1.4 (PA2), U2.38 (PA2)
PA3: J2.10, J5.16, U1.5 (PA3), U2.37 (PA3)
PA4: J2.9, J5.4, U1.6 (PA4), U2.36 (PA4)
PA5: J2.7, J5.17, U1.7 (PA5), U2.35 (PA5)
PA6: J2.5, J5.5, U1.8 (PA6), U2.34 (PA6)
PA7: J2.3, J5.18, U1.9 (PA7), U2.33 (PA7)
PB0: J1.4, J5.12, U1.10 (PB0), U2.1 (PB0)
PB1: J1.6, J5.24, U1.11 (PB1), U2.2 (PB1)
PB2: J1.8, J5.11, U1.12 (PB2), U2.3 (PB2)
PB3: J1.10, J5.23, U1.13 (PB3), U2.4 (PB3)
PB4: J1.9, J5.10, U1.14 (PB4), U2.5 (PB4)
PB5: J1.7, J5.22, U1.15 (PB5), U2.6 (PB5)
PB6: J1.5, J5.9, U1.16 (PB6), U2.7 (PB6)
PB7: J1.3, J5.21, U1.17 (PB7), U2.8 (PB7)
PHI2: J4.17, U1.25 (PHI2)
PS2CLK: J3.5, U2.16 (PD2)
PS2DATA: J3.1, U2.17 (PD3)
RESB: J4.3, U1.34 (RESB)
RWB: J4.13, U1.22 (RWB)
VCC: C1.2, C3.2, C6.1, C7.1, C8.2, J1.1, J2.1, J3.4, J4.2, J4.39, J5.1, J5.13, R1.1, U1.20 (VDD), U1.24 (CS1), U2.10 (VCC), U2.30 (AVCC), U3.16 (VCC)

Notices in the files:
README.md:
License:
Hardware designs are released under the [CERN Open Hardware Licence Version 2 – Permissive](https://ohwr.org/cern_ohl_p_v2.txt).
Firmware is released under the MIT License — [KEH Controller](./Firmware/KEH%20Controller/LICENSE), [PS2 Keyboard Controller](./Firmware/PS2%20Keyboard%20Controller/LICENSE), [STP Controller](./Firmware/STP%20Controller/LICENSE).
Hardware/Dev Output Board/Rev 1.0/Dev Output Board.kicad_pcb:
© 2024 A.C. Wright Design | acwrightdesign.com | Rev 1.0
